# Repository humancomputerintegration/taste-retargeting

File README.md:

# Taste Retargeting via Chemical Taste Modulators
This is the repository for the hardware schematics and compounds used in the "Taste Retargeting via Chemical Taste Modulators" paper (ACM UIST 2023). Thank you to [Alex Mazursky](https://www.alexmazursky.com/) for his help with the hardware design.

[Paper](https://lab.plopes.org/published/2023-UIST-TasteRetargeting-AuthorCopy.pdf)

**Original Paper Abstract:** Prior research has explored modifying taste through electrical stimulation. While promising, such interfaces often only elicit taste changes while in contact with the user’s tongue (e.g., cutlery with electrodes), making them incompatible with eating and swallowing real foods. Moreover, most interfaces cannot selectively alter basic tastes, but only the entire flavor profile (e.g., cannot selectively alter bitterness). To tackle this, we propose taste retargeting, a method of altering taste perception by delivering chemical modulators to the mouth before eating. These modulators temporarily change the response of taste receptors to foods, selectively suppressing or altering basic tastes. Our first study identified six accessible taste modulators that suppress salty, umami, sweet, or bitter and transform sour into sweet. Using these findings, we demonstrated an interactive application of this technique with the example of virtual reality, which we validated in our second study. We found that taste retargeting reduced the flavor mismatch between a food prop and other virtual foods.

## Hardware
To reproduce our experience, we include the KiCad files to manufacture our delivery mechanism. In addition to the PCB and included SMT components, the device uses a Seeeduino Xiao ESP32C3 and three mini peristaltic pumps (Takasago Fluidic Systems, RP-Q) connected to thin silicone tubing (ID = 1 mm; OD = 2 mm) via barbed connectors. Each tube is then connected to thinner PTFE tubing (ID = 0.6 mm, OD = 1 mm) leading to the mouth. We use silicone adhesive to connect silicone to PTFE. All three tubes are then attached to 20-gauge (0.8 mm thick, 8 mm loop diameter) lip cufs to hook at the mouth corners, which ensures the tubes stay in place.

## Modulators covered in paper
We propose interactively delivering taste modulators to alter taste perception while eating or drinking. However, given the lack of prior work in using taste modulators for interactive experiences, we had to identify and characterize a set of modulators that were accessible to realize our concept. Thus, we provide an overview of our modulators, including toxicological information. We specifically opted for easier access modulators (e.g., food safe, supplement, off-the-shelf, etc.), leading to modulators with suppressing or transforming effects. However, other modulators exist (e.g., demonstrated in mice or prescription medications) that might act as enhancers, which we discuss in Future Work.

### Gymnemic acids: sweet suppressor
Gymnema acids allows us to achieve sweet suppression. This is a chemical isolated from the leaves of Gymnema sylvestre. This leaf powder is a commonly available as a dietary supplement and thus food-safe; ours was purchased from Best Naturals. We use a concentration of 1.0% w/v based on Okamoto et al.

**Taste alteration mechanism:** Of our chosen modulators, this may be the most well-known, second only to miraculin. This sweet suppression has been attributed to its triterpene glycosides. More recently, Sanematsu et al. found that these gymnemic acids bind to the human sweet taste receptor hT1R3 to produce its sweet-suppressing effect.

### Clofibric acid: sweet and umami suppressor
Clofibric acid allows us to achieve simultaneous sweet & umami suppression. Clofibric acid (PubChem CID: [2797](https://pubchem.ncbi.nlm.nih.gov/compound/2797), Catalog #: 21608) was purchased from Cayman Chemical Company at its highest available purity (≥98%). We use a dose of 51.45 mg, based on Kochem & Breslin, well below its acute oral toxicity (LD50) of 897 mg/kg.

**Taste alteration mechanism:** Clofibric acid has been shown to be an antagonist for the sweet taste receptor (hT1R2-hT1R3), which also contributes to umami perception. In other words, clofibric acid binds and inhibits this receptor’s activity. This inhibition diminishes sweet and umami perception in humans.

### Lactisole: sweet and umami suppressor
Lactisole (PubChem CID: [16231](https://pubchem.ncbi.nlm.nih.gov/compound/16231), Catalog #: 18657) was purchased from Cayman Chemical Company at its highest available purity (≥98%). We use a dose of approximately 3.75 mg, based on Sclafani and Pérez. This modulator is approved for use in foods at levels up to 150 ppm (approximately 150 mg) per food item. Lactisole is a commonly used sweet modulator in industrial food processing [68]. The food industry typically uses lactisole to avoid perceiving an increase in sweetness when additional sugar is introduced for texture-purposes (e.g., softness).

**Taste alteration mechanism:** Lactisole achieves its sweet and umami suppression by blocking the activation of the hT1R2-hT1R3 receptor.

### Miraculin: sweet modulator
Miracle berry tablets are a commonly available food supplement derived from berries (Synsepalum dulcificum, known as “miracle fruit”). We source ours from the off-the-shelf product mberry. We use 200 mg of miracle berry dissolved in water. The key active ingredient, miraculin, produces the taste alteration. Miraculin is not associated with any safety concerns and does not represent a risk of allergy or toxicity to humans.

**Taste alteration mechanism:** Of our modulators, miraculin is the most recognizable as it is commercially advertised as a “party trick”. Miraculin binds to human sweet taste receptor hT1R2-hT1R3. While miraculin acts as an inhibitor at neutral pH environments, it functions as a strong agonist in the presence of acidic pH environments. In other words, miraculin causes acidic stimuli to activate a sweet taste receptor. This is why it is used as a “party trick” with acidic foods, such as making a lemon taste sweet. In addition, the perceived sourness of acidic stimuli is diminished, with mostly the sweet signal reaching the primary taste area. The exact mechanism of miraculin interaction with taste receptors remains unknown. However, miraculin interacts with lactisole, with psychophysical findings showing that lactisole diminishes the pH-dependent sweet response produced by miraculin.

### Zinc sulfate: sweet & bitter suppressor
Zinc sulfate (PubChem CID: [24424](https://pubchem.ncbi.nlm.nih.gov/compound/24424)) is a chemical commonly available in food supplements and has the U.S. Food and Drug Administration’s “Generally Regarded as Safe” status for food and beverages. We source it from an off-the-shelf product by Triquetra Health. We use a dose of 4 mg derived from pilots. Zinc sulfate’s acute oral toxicity (LD50) is 1,538 mg/kg.

**Taste alteration mechanism:** Zinc sulfate is a sweet inhibitor and selective bitter inhibitor. The exact mechanisms by which zinc ions affect sweet and bitter taste are still unknown, but Keast et al. suggests that they bind to taste receptors, altering their binding properties.

Since publishing the paper, we identified that Ionic Zinc's bitterness actually comes from another compound in the mixture, notably copper sulfate. We recommend experimenting with tablets that are largely zinc sulfate, such as Windmill or Puregen Labs Zinc Sulfate tablets, which are available on Amazon.

#### Amiloride: salty suppressor
Amiloride (PubChem CID: [16231](https://pubchem.ncbi.nlm.nih.gov/compound/16231), Catalog #: 14409) was purchased from Cayman Chemical Company at its highest available purity (≥98%). We use a dose of 1.722 mg, based on Schiffman et al.’s. This modulator’s acute oral toxicity (LD50) of this modulator is 300 mg/kg.

**Taste alteration mechanism:** Amiloride has been used as a specific inhibitor of sodium transport (reducing saltiness). The psychophysical findings that amiloride reduces the intensity of taste perception of sodium and lithium salts is consistent with its action in which the fluxes of sodium and lithium are molecularly blocked.

## Citation
When using or building upon this work **in an academic publication**, please consider citing our paper:

Jas Brooks, Noor Amin, and Pedro Lopes. 2023. “Taste Retargeting via Chemical Taste Modulators.” In Proceedings of ACM Symposium on User Interface Software and Technology 2023 (UIST ’23). Association for Computing Machinery, New York, NY, USA. DOI:10.1145/3586183.3606818

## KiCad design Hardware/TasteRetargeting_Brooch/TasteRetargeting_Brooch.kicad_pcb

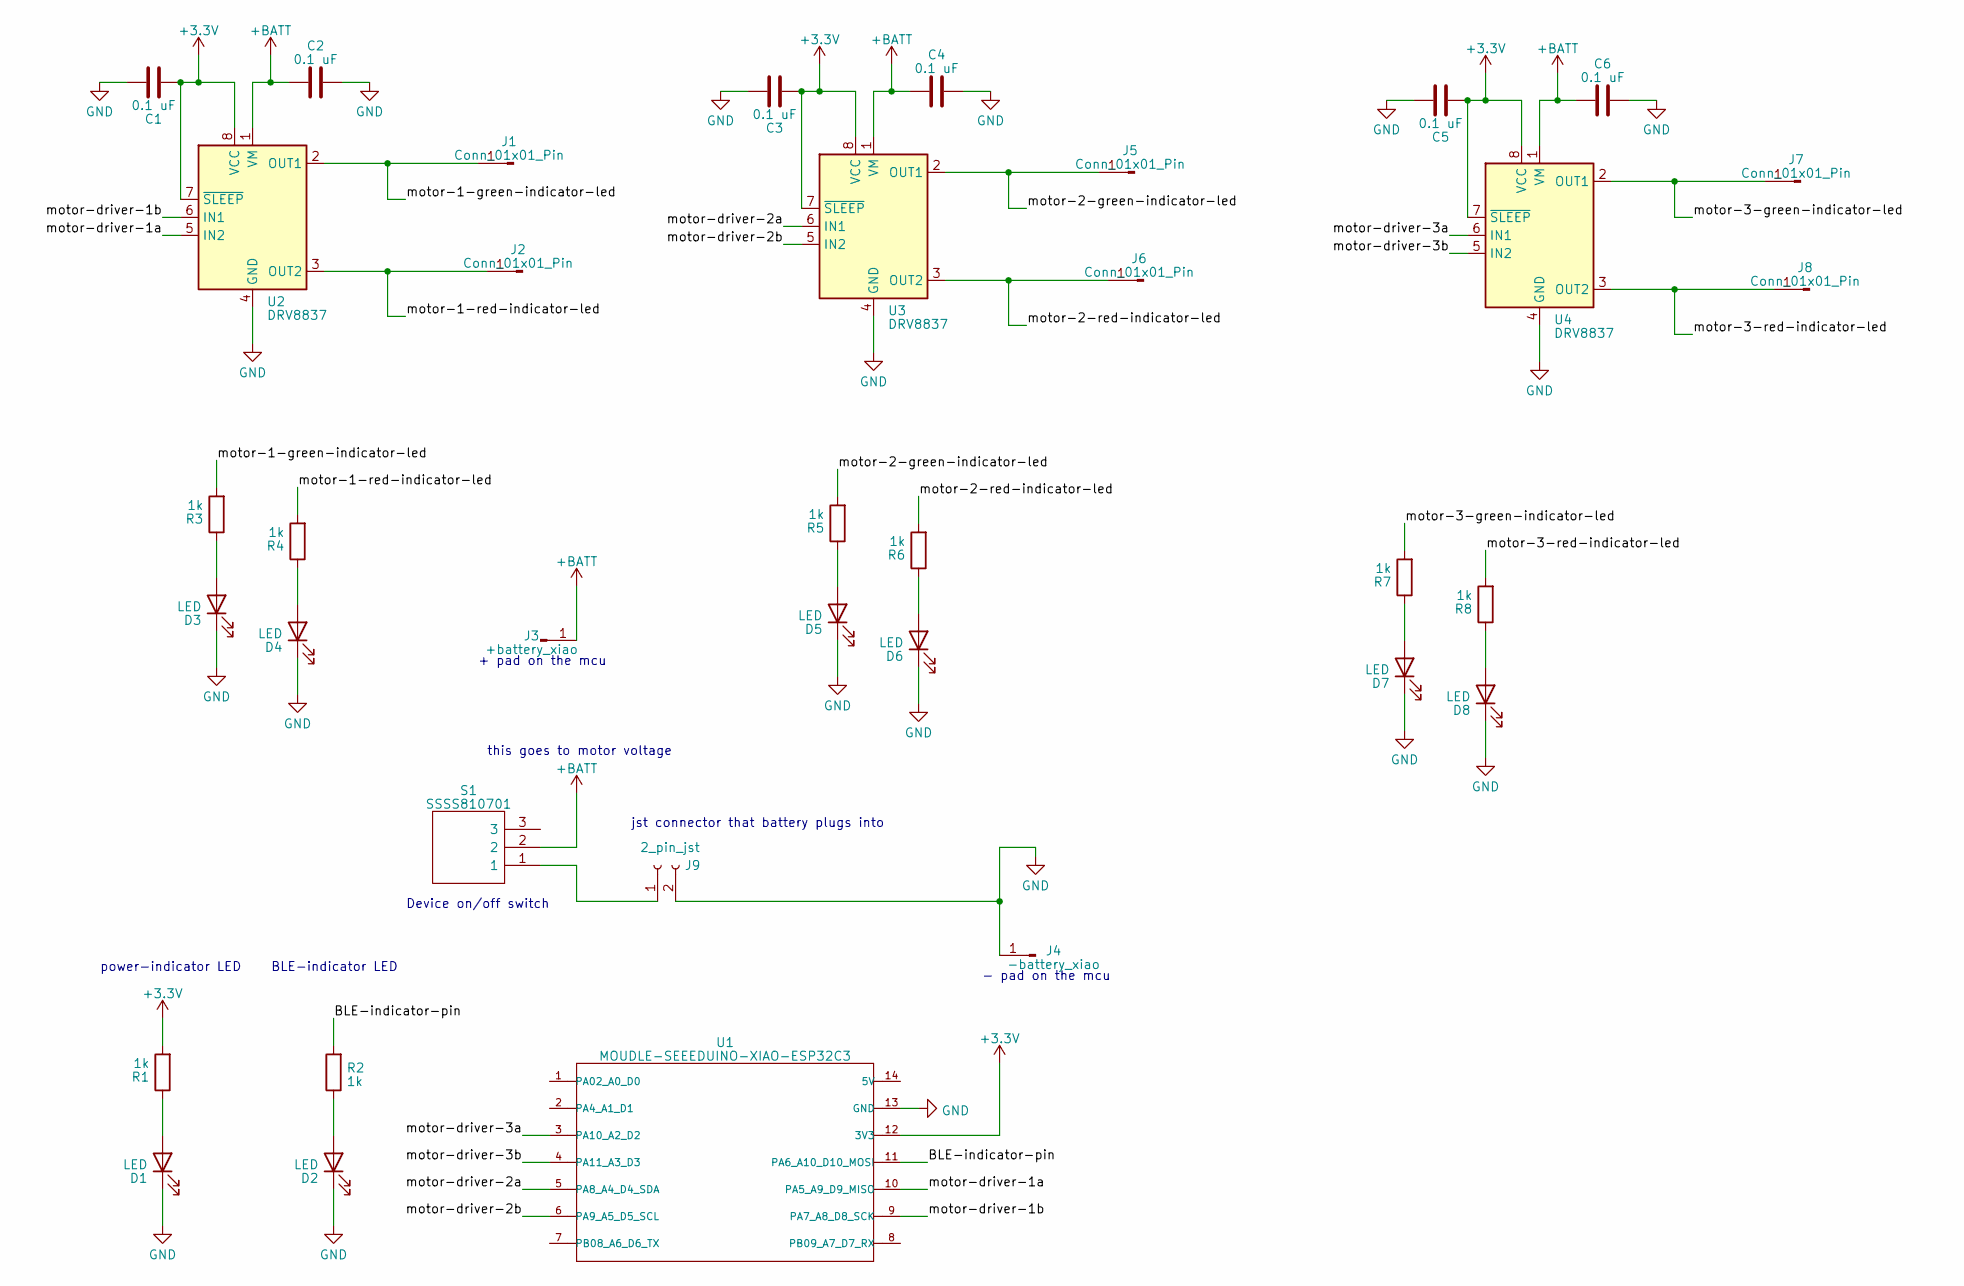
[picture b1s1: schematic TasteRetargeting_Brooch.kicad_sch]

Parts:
C1, C2, C3, C4, C5, C6: 0.1 uF; C_0603_1608Metric
D1, D2, D3, D4, D5, D6, D7, D8: LED; LED_0603_1608Metric
J1, J2, J5, J6, J7, J8: Conn_01x01_Pin; TestPoint_Loop_D1.80mm_Drill1.0mm_Beaded
J3: +battery_xiao; TestPoint_Pad_1.0x1.0mm
J4: -battery_xiao; TestPoint_Pad_1.0x1.0mm
J9: 2_pin_jst; JST_PH_S2B-PH-K_1x02_P2.00mm_Horizontal
R1, R2, R3, R4, R5, R6, R7, R8: 1k; R_0603_1608Metric
S1: SSSS810701; Manufacturer_Part_Number SSSS810701; Mouser Part Number 688-SSSS810701
U1: MOUDLE-SEEEDUINO-XIAO-ESP32C3; MOUDLE14P-SMD-2.54-21X17.8MM
U2, U3, U4: DRV8837; WSON-8-1EP_2x2mm_P0.5mm_EP0.9x1.6mm

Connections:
+3.3V: C1.1, C3.1, C5.1, R1.2, U1.12 (3V3), U2.7 (~SLEEP), U2.8 (VCC), U3.7 (~SLEEP), U3.8 (VCC), U4.7 (~SLEEP), U4.8 (VCC)
+BATT: C2.1, C4.1, C6.1, J3.1, S1.2, U2.1 (VM), U3.1 (VM), U4.1 (VM)
/BLE-indicator-pin: R2.2, U1.11 (PA6_A10_D10_MOSI)
/motor-1-green-indicator-led: J1.1, R3.2, U2.2 (OUT1)
/motor-1-red-indicator-led: J2.1, R4.2, U2.3 (OUT2)
/motor-2-green-indicator-led: J5.1, R5.2, U3.2 (OUT1)
/motor-2-red-indicator-led: J6.1, R6.2, U3.3 (OUT2)
/motor-3-green-indicator-led: J7.1, R7.2, U4.2 (OUT1)
/motor-3-red-indicator-led: J8.1, R8.2, U4.3 (OUT2)
/motor-driver-1a: U1.10 (PA5_A9_D9_MISO), U2.5 (IN2)
/motor-driver-1b: U1.9 (PA7_A8_D8_SCK), U2.6 (IN1)
/motor-driver-2a: U1.5 (PA8_A4_D4_SDA), U3.6 (IN1)
/motor-driver-2b: U1.6 (PA9_A5_D5_SCL), U3.5 (IN2)
/motor-driver-3a: U1.3 (PA10_A2_D2), U4.6 (IN1)
/motor-driver-3b: U1.4 (PA11_A3_D3), U4.5 (IN2)
GND: C1.2, C2.2, C3.2, C4.2, C5.2, C6.2, D1.1 (K), D2.1 (K), D3.1 (K), D4.1 (K), D5.1 (K), D6.1 (K), D7.1 (K), D8.1 (K), J4.1, J9.2, U1.13 (GND), U2.4 (GND), U2.9 (GND), U3.4 (GND), U3.9 (GND), U4.4 (GND), U4.9 (GND)
unnamed: D1.2 (A), R1.1
unnamed: D2.2 (A), R2.1
unnamed: D3.2 (A), R3.1
unnamed: D4.2 (A), R4.1
unnamed: D5.2 (A), R5.1
unnamed: D6.2 (A), R6.1
unnamed: D7.2 (A), R7.1
unnamed: D8.2 (A), R8.1
unnamed: J9.1, S1.1

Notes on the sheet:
- pad on the mcu
Device on/off switch
this goes to motor voltage
BLE-indicator LED
power-indicator LED
jst connector that battery plugs into
+ pad on the mcu

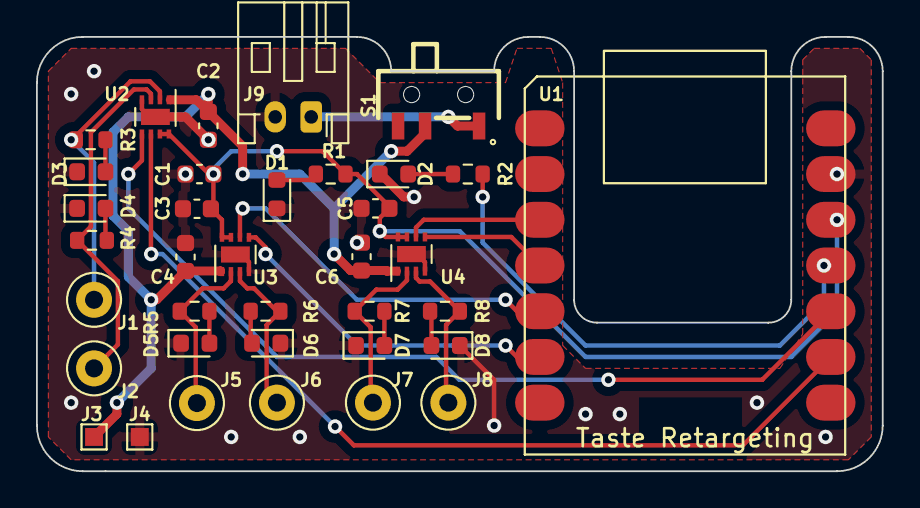
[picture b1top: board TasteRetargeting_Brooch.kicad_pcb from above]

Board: 2 copper layers, 47.0 x 24.1 mm, 36 parts (0 on the bottom side), 25 nets.

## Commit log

2023-11-06 Adding the schematics and PCB for Taste Retargeting's hardware (brooch).
